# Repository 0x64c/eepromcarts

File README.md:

# eepromcarts

A collection of EEPROM software development cartridges for various 8/16-bit consoles.

## Watara Supervision

A SV cartridge design is complete with support for:
* 1Mbit ROM size
* 4 DIP-selectable ROM banks

## Sega Megadrive

A Megadrive cartridge design is complete, with support for:
* 4Mbit ROM size
* 256Kbit FRAM

## GameBoy

A GB cartridge design is complete with support for:
* 256Kbit FRAM
* RTC
* Bank switching through CPLD

## Sega Master System

A SMS cartridge is planned with support for:
* 256Kbit FRAM
* Bank switching
* 1-4Mbit rom size

## Super Famicom

A SFC cartridge is planned with support for:
* 256Kbit FRAM
* RTC?
* CIC (donor IC)
* Some expansion IC's

## EEPROM Writer

A cheap, slow EEPROM reader/writer:
* Program/read one PLCC32 EEPROM at once
* Don't build this if you already have a real programmer, or an arduino and some shift registers

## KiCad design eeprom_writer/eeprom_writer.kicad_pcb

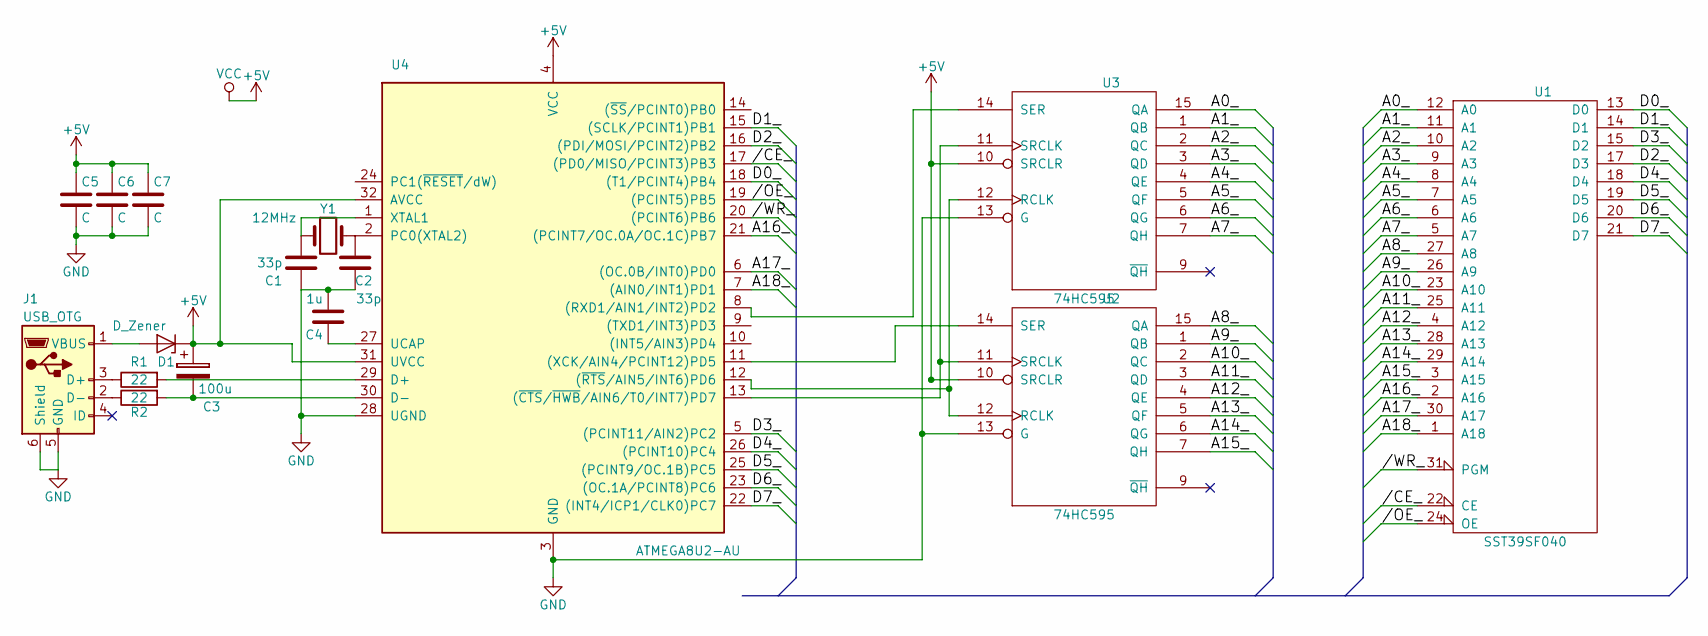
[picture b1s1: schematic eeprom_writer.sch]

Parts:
C1, C2: 33p; C_0603
C3: 100u
C4: 1u; C_0603
C5, C6, C7: C; C_0603
D1: D_Zener
J1: USB_OTG
R1, R2: 22
U1: SST39SF040; PLCC-32_SMD-Socket
U2, U3: 74HC595
U4: ATMEGA8U2-AU; TQFP-32
Y1: 12MHz

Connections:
+5V: C3.1, C5.1, C6.1, C7.1, D1.1 (K), U1.32 (VCC), U2.10 (SRCLR), U2.16 (VCC), U3.10 (SRCLR), U3.16 (VCC), U4.4 (VCC), U4.31 (UVCC), U4.32 (AVCC)
//CE_: U1.22 (CE), U4.17 ((PD0/MISO/PCINT3)PB3)
//OE_: U1.24 (OE), U4.19 ((PCINT5)PB5)
//WR_: U1.31 (PGM), U4.20 ((PCINT6)PB6)
/A0_: U1.12 (A0), U3.15 (QA)
/A1_: U1.11 (A1), U3.1 (QB)
/A2_: U1.10 (A2), U3.2 (QC)
/A3_: U1.9 (A3), U3.3 (QD)
/A4_: U1.8 (A4), U3.4 (QE)
/A5_: U1.7 (A5), U3.5 (QF)
/A6_: U1.6 (A6), U3.6 (QG)
/A7_: U1.5 (A7), U3.7 (QH)
/A8_: U1.27 (A8), U2.15 (QA)
/A9_: U1.26 (A9), U2.1 (QB)
/A10_: U1.23 (A10), U2.2 (QC)
/A11_: U1.25 (A11), U2.3 (QD)
/A12_: U1.4 (A12), U2.4 (QE)
/A13_: U1.28 (A13), U2.5 (QF)
/A14_: U1.29 (A14), U2.6 (QG)
/A15_: U1.3 (A15), U2.7 (QH)
/A16_: U1.2 (A16), U4.21 ((PCINT7/OC.0A/OC.1C)PB7)
/A17_: U1.30 (A17), U4.6 ((OC.0B/INT0)PD0)
/A18_: U1.1 (A18), U4.7 ((AIN0/INT1)PD1)
/D0_: U1.13 (D0), U4.18 ((T1/PCINT4)PB4)
/D1_: U1.14 (D1), U4.15 ((SCLK/PCINT1)PB1)
/D2_: U1.17 (D3), U4.16 ((PDI/MOSI/PCINT2)PB2)
/D3_: U1.15 (D2), U4.5 ((PCINT11/AIN2)PC2)
/D4_: U1.18 (D4), U4.26 ((PCINT10)PC4)
/D5_: U1.19 (D5), U4.25 ((PCINT9/OC.1B)PC5)
/D6_: U1.20 (D6), U4.23 ((OC.1A/PCINT8)PC6)
/D7_: U1.21 (D7), U4.22 ((INT4/ICP1/CLK0)PC7)
GND: C1.1, C2.1, C4.2, C5.2, C6.2, C7.2, J1.5 (GND), J1.6 (Shield), U1.16 (GND), U2.8 (GND), U2.13 (G), U3.8 (GND), U3.13 (G), U4.3 (GND), U4.28 (UGND)
unnamed: C1.2, U4.1 (XTAL1), Y1.1
unnamed: C2.2, U4.2 (PC0(XTAL2)), Y1.2
unnamed: C3.2, R2.2, U4.30 (D-)
unnamed: C4.1, U4.27 (UCAP)
unnamed: D1.2 (A), J1.1 (VBUS)
unnamed: J1.2 (D-), R2.1
unnamed: J1.3 (D+), R1.1
unnamed: R1.2, U4.29 (D+)
unnamed: U2.11 (SRCLK), U3.11 (SRCLK), U4.13 ((~CTS~/~HWB~/AIN6/T0/INT7)PD7)
unnamed: U2.12 (RCLK), U3.12 (RCLK), U4.12 ((~RTS~/AIN5/INT6)PD6)
unnamed: U2.14 (SER), U4.11 ((XCK/AIN4/PCINT12)PD5)
unnamed: U3.14 (SER), U4.8 ((RXD1/AIN1/INT2)PD2)

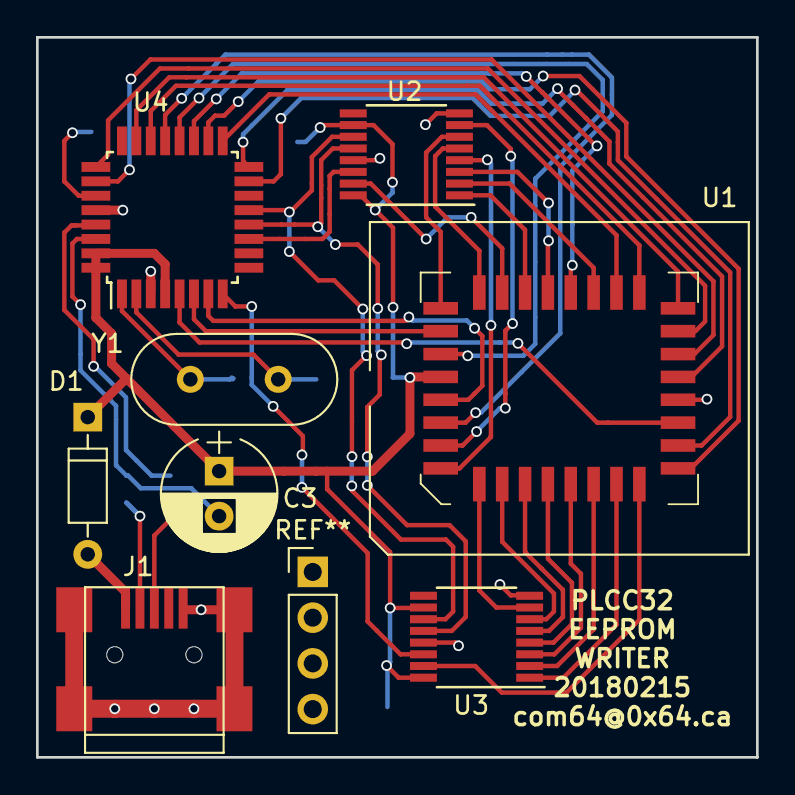
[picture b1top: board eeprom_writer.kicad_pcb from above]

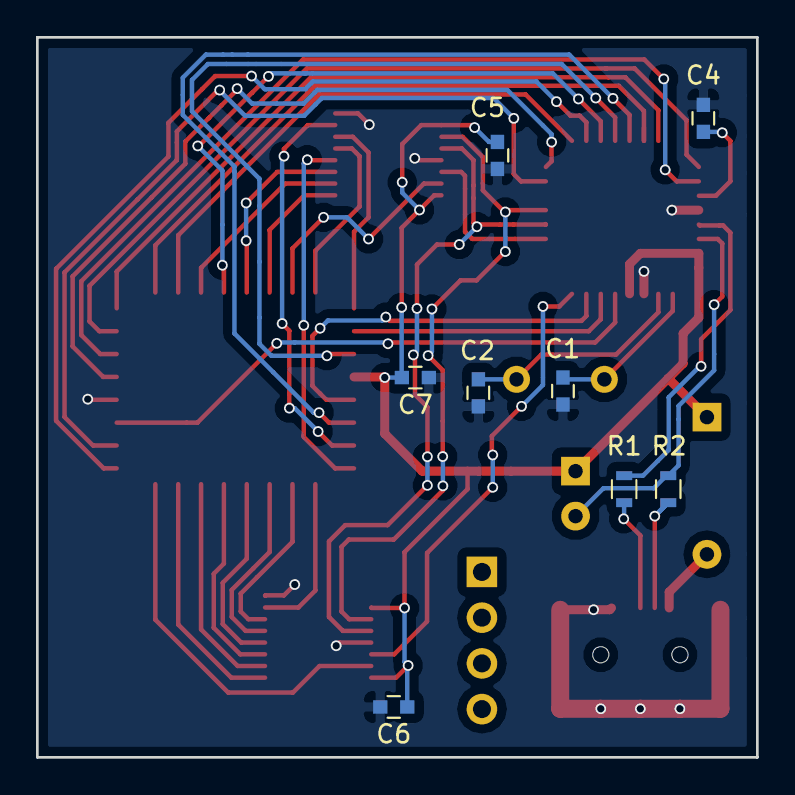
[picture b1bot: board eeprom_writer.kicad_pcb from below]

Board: 2 copper layers, 40.0 x 40.0 mm, 16 parts (8 on the bottom side), 44 nets.

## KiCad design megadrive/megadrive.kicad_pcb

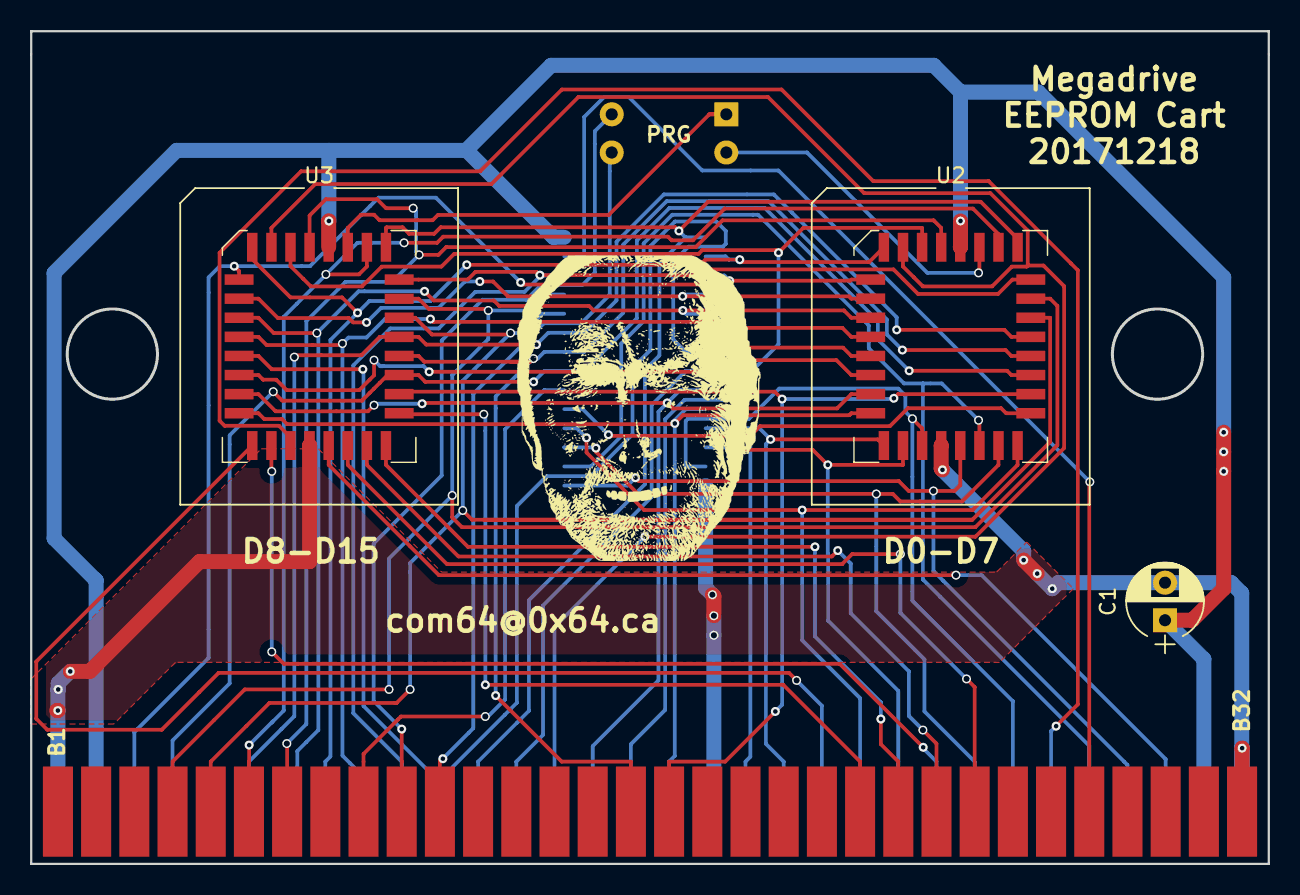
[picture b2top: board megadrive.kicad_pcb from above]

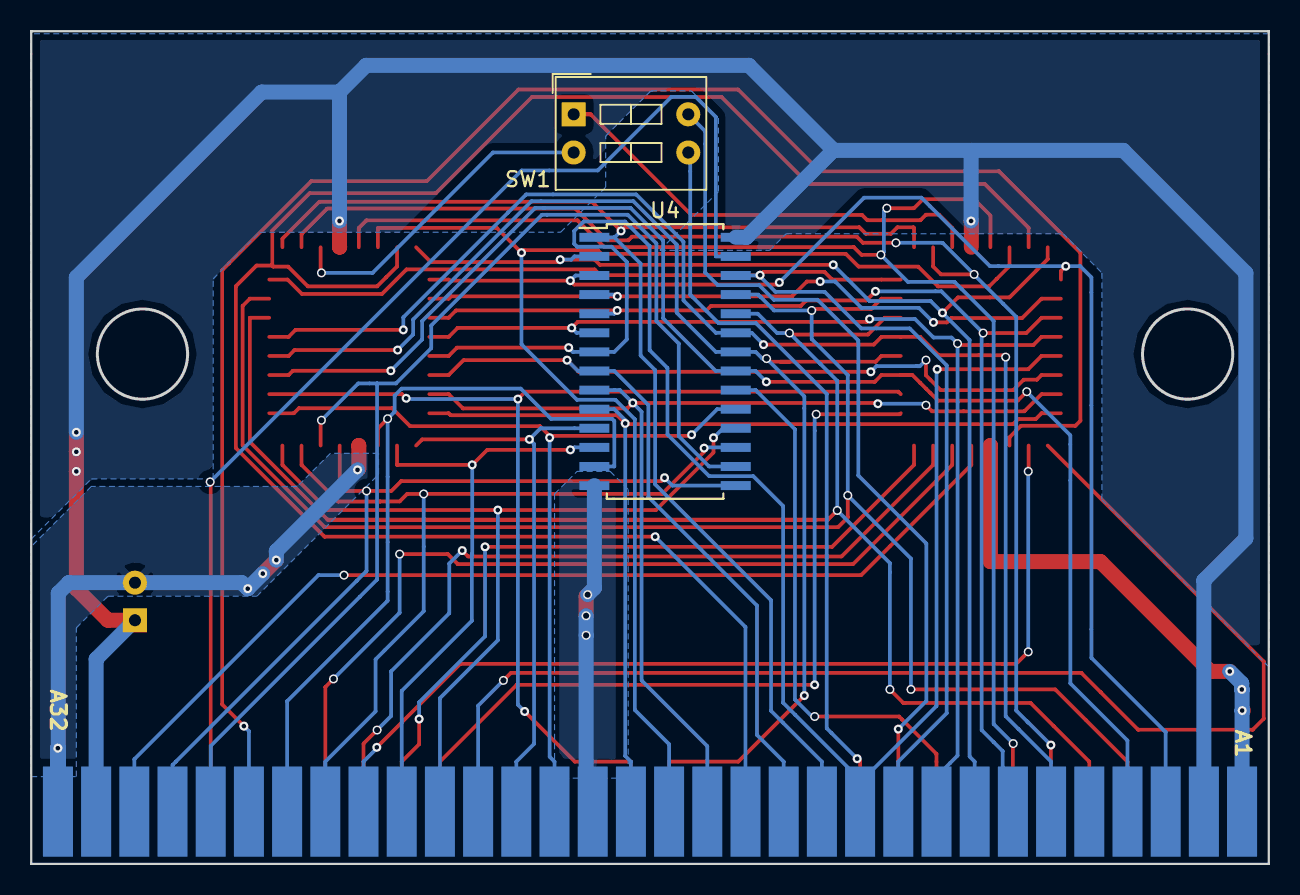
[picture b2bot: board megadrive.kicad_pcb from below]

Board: 2 copper layers, 82.3 x 55.4 mm, 6 parts (2 on the bottom side), 45 nets.

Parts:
C1: CP; CP_Radial_D5.0mm_P2.50mm
SW1: SW_DIP_x02; SW_DIP_x2_W7.62mm_Slide
U1: MD_CART
U2, U3: SST39SF040; PLCC-32_SMD-Socket
U4: FM1808B-SG; SOIC-28W_7.5x17.9mm_Pitch1.27mm

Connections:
+5V: C1.1, U1.2, U1.31, U2.32, U3.32, U4.28
//CE: U1.49, U2.22, U3.22
//OE: U1.48, U2.24, U3.24, U4.22
//WR: U1.60, U4.27
/A1: U1.17, U2.12, U3.12, U4.10
/A2: U1.15, U2.11, U3.11, U4.9
/A3: U1.13, U2.10, U3.10, U4.8
/A4: U1.11, U2.9, U3.9, U4.7
/A5: U1.9, U2.8, U3.8, U4.6
/A6: U1.7, U2.7, U3.7, U4.5
/A7: U2.6, U3.6, U4.4
/A8: U1.3, U2.5, U3.5, U4.3
/A9: U1.36, U2.27, U3.27, U4.25
/A10: U1.37, U2.26, U3.26, U4.24
/A11: U1.4, U2.23, U3.23, U4.21
/A12: U1.6, U2.25, U3.25, U4.23
/A13: U1.8, U2.4, U3.4, U4.2
/A14: U1.10, U2.28, U3.28, U4.26
/A15: U1.12, U2.29, U3.29, U4.1
/A16: U1.14, U2.3, U3.3
/A17: U1.16, U2.2, U3.2
/A18: U1.38, U2.30, U3.30
/A19: U1.39, U2.1, U3.1
/A21: U1.41, U4.20
/A22: SW1.4, U1.42
/A23: SW1.3, U1.43
/D0: U1.20, U2.13, U4.11
/D1: U1.23, U2.14, U4.12
/D2: U1.26, U2.15, U4.13
/D3: U1.29, U2.17, U4.15
/D4: U1.28, U2.18, U4.16
/D5: U1.25, U2.19, U4.17
/D6: U1.22, U2.20, U4.18
/D7: U1.19, U2.21, U4.19
/D8: U1.21, U3.13
/D9: U1.24, U3.14
/D10: U1.27, U3.15
/D11: U1.30, U3.17
/D12: U1.57, U3.18
/D13: U1.56, U3.19
/D14: U1.55, U3.20
/D15: U1.54, U3.21
GND: C1.2, U1.1, U1.18, U1.32, U1.64, U2.16, U3.16, U4.14
unnamed: SW1.1, U3.31
unnamed: SW1.2, U2.31

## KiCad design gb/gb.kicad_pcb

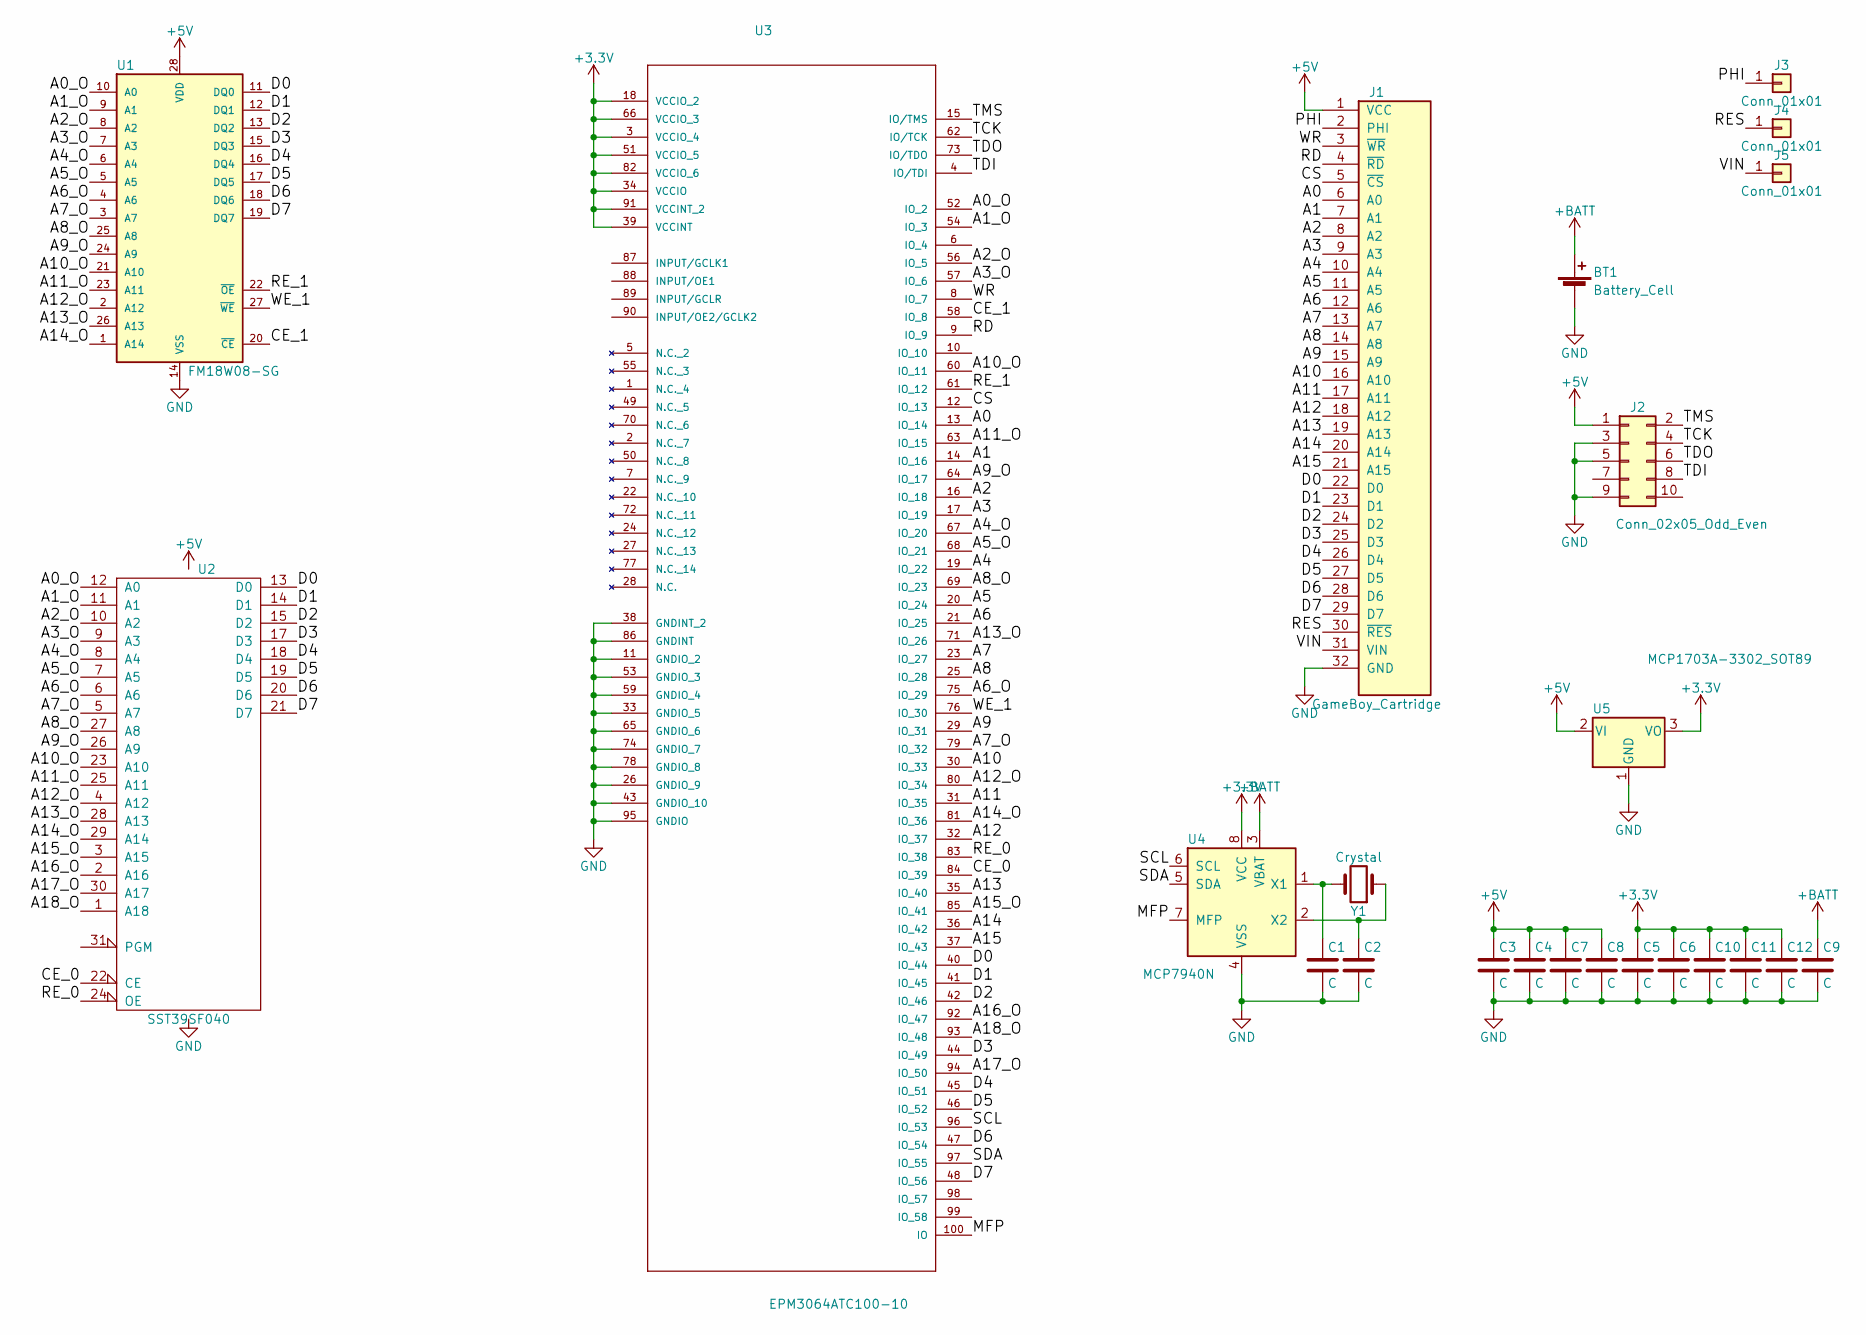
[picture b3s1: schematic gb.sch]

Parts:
BT1: Battery_Cell; Keystone_3001_1x12mm-CoinCell
C1, C2, C3, C4, C5, C6, C7, C8, C9, C10, C11, C12: C; C_1206_HandSoldering
J1: GameBoy_Cartridge; GameBoy_Cartridge_1x32_P1.50mm_Edge
J2: Conn_02x05_Odd_Even; Pin_Header_Straight_2x05_Pitch2.54mm
J3, J4, J5: Conn_01x01; pad
U1: FM18W08-SG; SOIC-28W_7.5x17.9mm_Pitch1.27mm
U2: SST39SF040; PLCC-32_SMD-Socket
U3: EPM3064ATC100-10
U4: MCP7940N; SOIC-8_3.9x4.9mm_Pitch1.27mm
U5: MCP1703A-3302_SOT89; SOT-89-3_Handsoldering
Y1: Crystal; Crystal_HC52-U_Vertical

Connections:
+3V3: C5.1, C6.1, C10.1, C11.1, C12.1, U3.3 (VCCIO_4), U3.18 (VCCIO_2), U3.34 (VCCIO), U3.39 (VCCINT), U3.51 (VCCIO_5), U3.66 (VCCIO_3), U3.82 (VCCIO_6), U3.91 (VCCINT_2), U4.8 (VCC), U5.3 (VO)
+5V: C3.1, C4.1, C7.1, C8.1, J1.1 (VCC), J2.1, U1.28 (VDD), U2.32 (VCC), U5.2 (VI)
+BATT: BT1.1 (+), C9.1, U4.3 (VBAT)
/A0: J1.6 (A0), U3.13 (IO_14)
/A0_O: U1.10 (A0), U2.12 (A0), U3.52 (IO_2)
/A1: J1.7 (A1), U3.14 (IO_16)
/A1_O: U1.9 (A1), U2.11 (A1), U3.54 (IO_3)
/A2: J1.8 (A2), U3.16 (IO_18)
/A2_O: U1.8 (A2), U2.10 (A2), U3.56 (IO_5)
/A3: J1.9 (A3), U3.17 (IO_19)
/A3_O: U1.7 (A3), U2.9 (A3), U3.57 (IO_6)
/A4: J1.10 (A4), U3.19 (IO_22)
/A4_O: U1.6 (A4), U2.8 (A4), U3.67 (IO_20)
/A5: J1.11 (A5), U3.20 (IO_24)
/A5_O: U1.5 (A5), U2.7 (A5), U3.68 (IO_21)
/A6: J1.12 (A6), U3.21 (IO_25)
/A6_O: U1.4 (A6), U2.6 (A6), U3.75 (IO_29)
/A7: J1.13 (A7), U3.23 (IO_27)
/A7_O: U1.3 (A7), U2.5 (A7), U3.79 (IO_32)
/A8: J1.14 (A8), U3.25 (IO_28)
/A8_O: U1.25 (A8), U2.27 (A8), U3.69 (IO_23)
/A9: J1.15 (A9), U3.29 (IO_31)
/A9_O: U1.24 (A9), U2.26 (A9), U3.64 (IO_17)
/A10: J1.16 (A10), U3.30 (IO_33)
/A10_O: U1.21 (A10), U2.23 (A10), U3.60 (IO_11)
/A11: J1.17 (A11), U3.31 (IO_35)
/A11_O: U1.23 (A11), U2.25 (A11), U3.63 (IO_15)
/A12: J1.18 (A12), U3.32 (IO_37)
/A12_O: U1.2 (A12), U2.4 (A12), U3.80 (IO_34)
/A13: J1.19 (A13), U3.35 (IO_40)
/A13_O: U1.26 (A13), U2.28 (A13), U3.71 (IO_26)
/A14: J1.20 (A14), U3.36 (IO_42)
/A14_O: U1.1 (A14), U2.29 (A14), U3.81 (IO_36)
/A15: J1.21 (A15), U3.37 (IO_43)
/A15_O: U2.3 (A15), U3.85 (IO_41)
/A16_O: U2.2 (A16), U3.92 (IO_47)
/A17_O: U2.30 (A17), U3.94 (IO_50)
/A18_O: U2.1 (A18), U3.93 (IO_48)
/CE_0: U2.22 (CE), U3.84 (IO_39)
/CE_1: U1.20 (~CE~), U3.58 (IO_8)
/CS: J1.5 (~CS), U3.12 (IO_13)
/D0: J1.22 (D0), U1.11 (DQ0), U2.13 (D0), U3.40 (IO_44)
/D1: J1.23 (D1), U1.12 (DQ1), U2.14 (D1), U3.41 (IO_45)
/D2: J1.24 (D2), U1.13 (DQ2), U2.15 (D2), U3.42 (IO_46)
/D3: J1.25 (D3), U1.15 (DQ3), U2.17 (D3), U3.44 (IO_49)
/D4: J1.26 (D4), U1.16 (DQ4), U2.18 (D4), U3.45 (IO_51)
/D5: J1.27 (D5), U1.17 (DQ5), U2.19 (D5), U3.46 (IO_52)
/D6: J1.28 (D6), U1.18 (DQ6), U2.20 (D6), U3.47 (IO_54)
/D7: J1.29 (D7), U1.19 (DQ7), U2.21 (D7), U3.48 (IO_56)
/MFP: U3.100 (IO), U4.7 (MFP)
/PHI: J1.2 (PHI), J3.1
/RD: J1.4 (~RD), U3.9 (IO_9)
/RES: J1.30 (~RES), J4.1
/RE_0: U2.24 (OE), U3.83 (IO_38)
/RE_1: U1.22 (~OE~), U3.61 (IO_12)
/SCL: U3.96 (IO_53), U4.6 (SCL)
/SDA: U3.97 (IO_55), U4.5 (SDA)
/TCK: J2.4, U3.62 (IO/TCK)
/TDI: J2.8, U3.4 (IO/TDI)
/TDO: J2.6, U3.73 (IO/TDO)
/TMS: J2.2, U3.15 (IO/TMS)
/VIN: J1.31 (VIN), J5.1
/WE_1: U1.27 (~WE~), U3.76 (IO_30)
/WR: J1.3 (~WR), U3.8 (IO_7)
GND: BT1.2 (-), C1.2, C2.2, C3.2, C4.2, C5.2, C6.2, C7.2, C8.2, C9.2, C10.2, C11.2, C12.2, J1.32 (GND), J2.3, J2.5, J2.9, U1.14 (VSS), U2.16 (GND), U3.11 (GNDIO_2), U3.26 (GNDIO_9), U3.33 (GNDIO_5), U3.38 (GNDINT_2), U3.43 (GNDIO_10), U3.53 (GNDIO_3), U3.59 (GNDIO_4), U3.65 (GNDIO_6), U3.74 (GNDIO_7), U3.78 (GNDIO_8), U3.86 (GNDINT), U3.95 (GNDIO), U4.4 (VSS), U5.1 (GND)
unnamed: C1.1, U4.1 (X1), Y1.2
unnamed: C2.1, U4.2 (X2), Y1.1

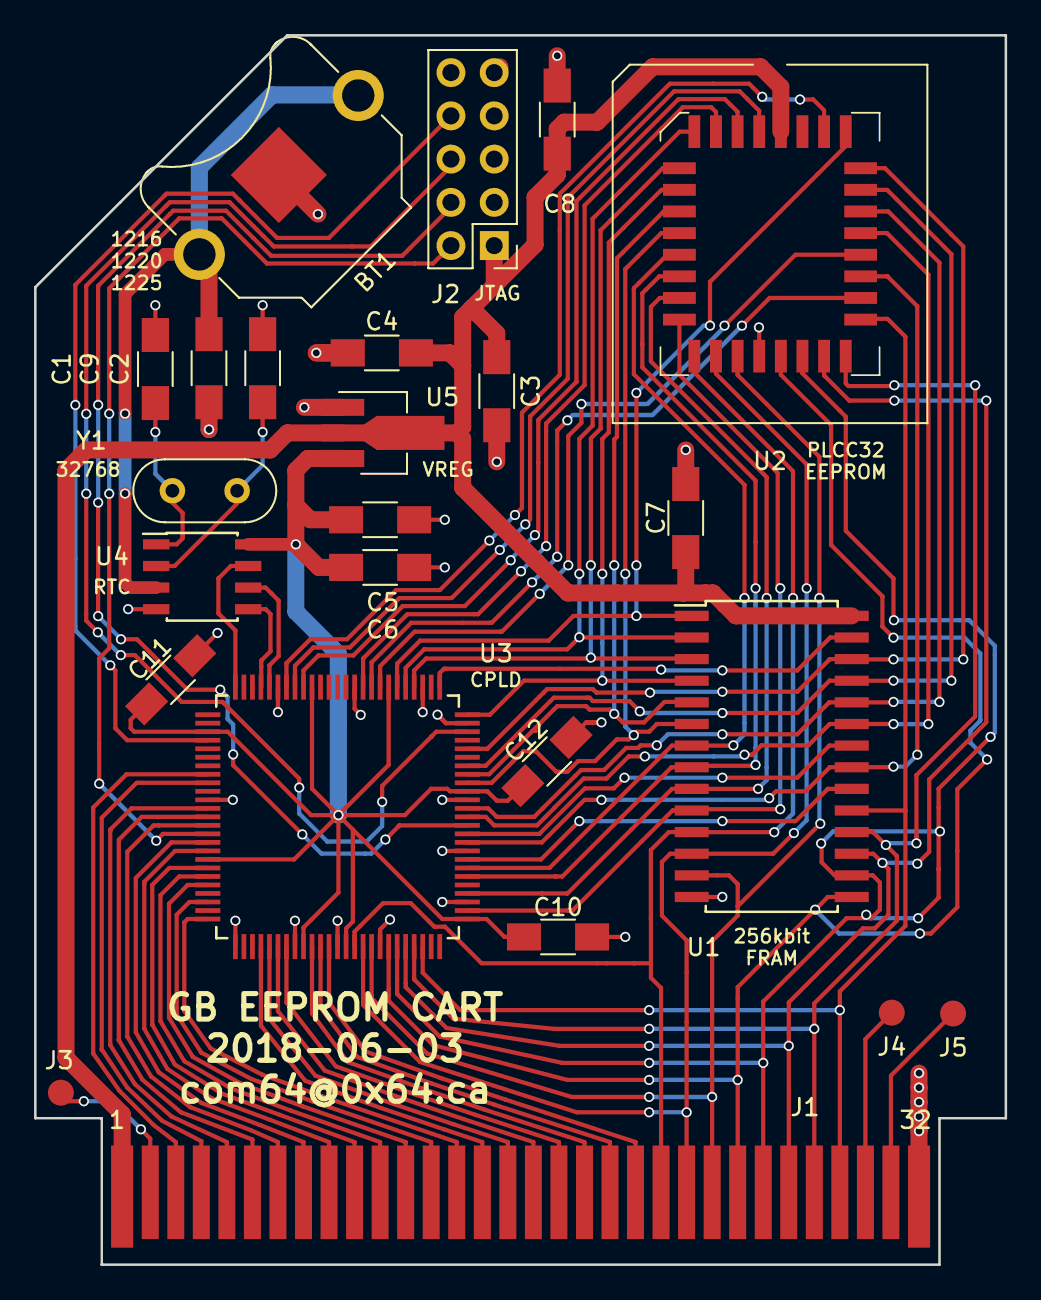
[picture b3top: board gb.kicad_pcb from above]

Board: 2 copper layers, 57.0 x 72.2 mm, 24 parts (0 on the bottom side), 67 nets.

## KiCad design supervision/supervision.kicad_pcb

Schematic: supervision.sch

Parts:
C1: 100n; C_Disc_D5.0mm_W2.5mm_P2.50mm
C2: 10u; CP_Radial_D4.0mm_P1.50mm
J1, J2: Conn_01x01; PAD
RN1: R_Network03; R_Array_SIP4
SW1: SW_DIP_x05; SMDIP-10_W9.53mm
U1: SST39SF040; PLCC-32
U2: SV_CART; SV_EDGE

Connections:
+5V: C1.1, C2.1, RN1.1 (common), U1.32 (VCC), U2.40
//CE: SW1.5, U1.24 (OE), U2.1
/A0: U1.12 (A0), U2.2
/A1: U1.11 (A1), U2.3
/A2: U1.10 (A2), U2.4
/A3: U1.9 (A3), U2.5
/A4: U1.8 (A4), U2.6
/A5: U1.7 (A5), U2.7
/A6: U1.6 (A6), U2.8
/A7: U1.5 (A7), U2.9
/A8: U1.27 (A8), U2.10
/A9: U1.26 (A9), U2.11
/A10: U1.23 (A10), U2.12
/A11: U1.25 (A11), U2.13
/A12: U1.4 (A12), U2.14
/A13: U1.28 (A13), U2.15
/A14: U1.29 (A14), U2.16
/A15: U1.3 (A15), U2.17
/A16: RN1.4 (R3), SW1.10, U1.2 (A16), U2.18
/A17: RN1.2 (R1), SW1.8, U1.30 (A17)
/A18: RN1.3 (R2), SW1.9, U1.1 (A18)
/D0: U1.13 (D0), U2.34
/D1: U1.14 (D1), U2.33
/D2: U1.15 (D2), U2.32
/D3: U1.17 (D3), U2.31
/D4: U1.18 (D4), U2.30
/D5: U1.19 (D5), U2.29
/D6: U1.20 (D6), U2.28
/D7: U1.21 (D7), U2.27
GND: C1.2, C2.2, SW1.1, SW1.2, SW1.3, U1.16 (GND), U2.21, U2.22
unnamed: J1.1, SW1.6, U1.22 (CE)
unnamed: J2.1, U2.19
unnamed: SW1.4, U2.20
unnamed: SW1.7, U1.31 (PGM)

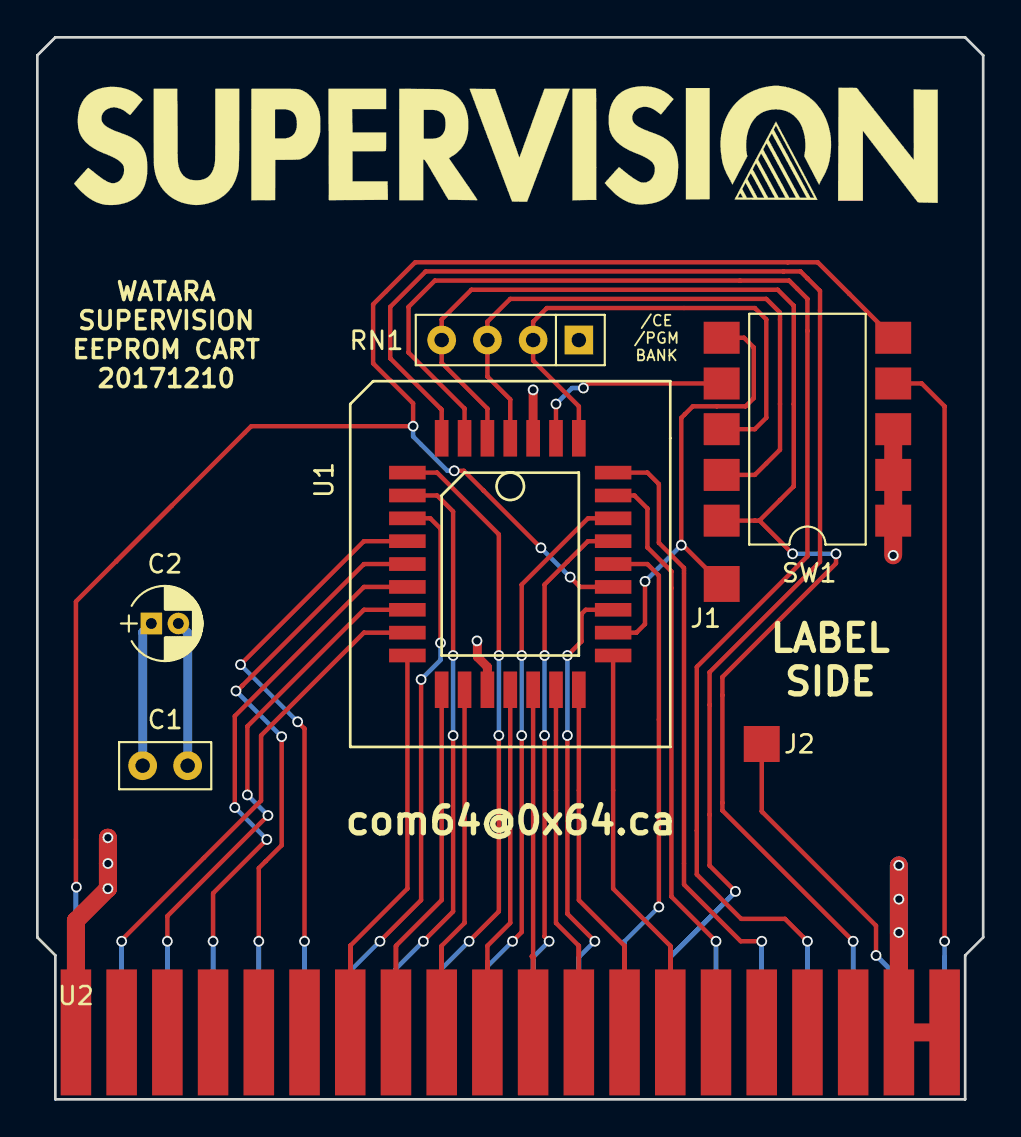
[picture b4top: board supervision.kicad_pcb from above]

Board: 2 copper layers, 52.5 x 59.0 mm, 8 parts (0 on the bottom side), 34 nets.

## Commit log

2018-02-14 initial commit: add Watara Supervision design
2018-02-14 Added megadrive and .kicad_mod files, cleaned up supervision files
2018-02-15 add eeprom_writer files: cheap, slow eeprom programmer
2018-06-04 Updated MD, SV, Writer; added GB

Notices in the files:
parts and their libraries:
Copyright 2016 Accelerated Designs. All rights reserved.
